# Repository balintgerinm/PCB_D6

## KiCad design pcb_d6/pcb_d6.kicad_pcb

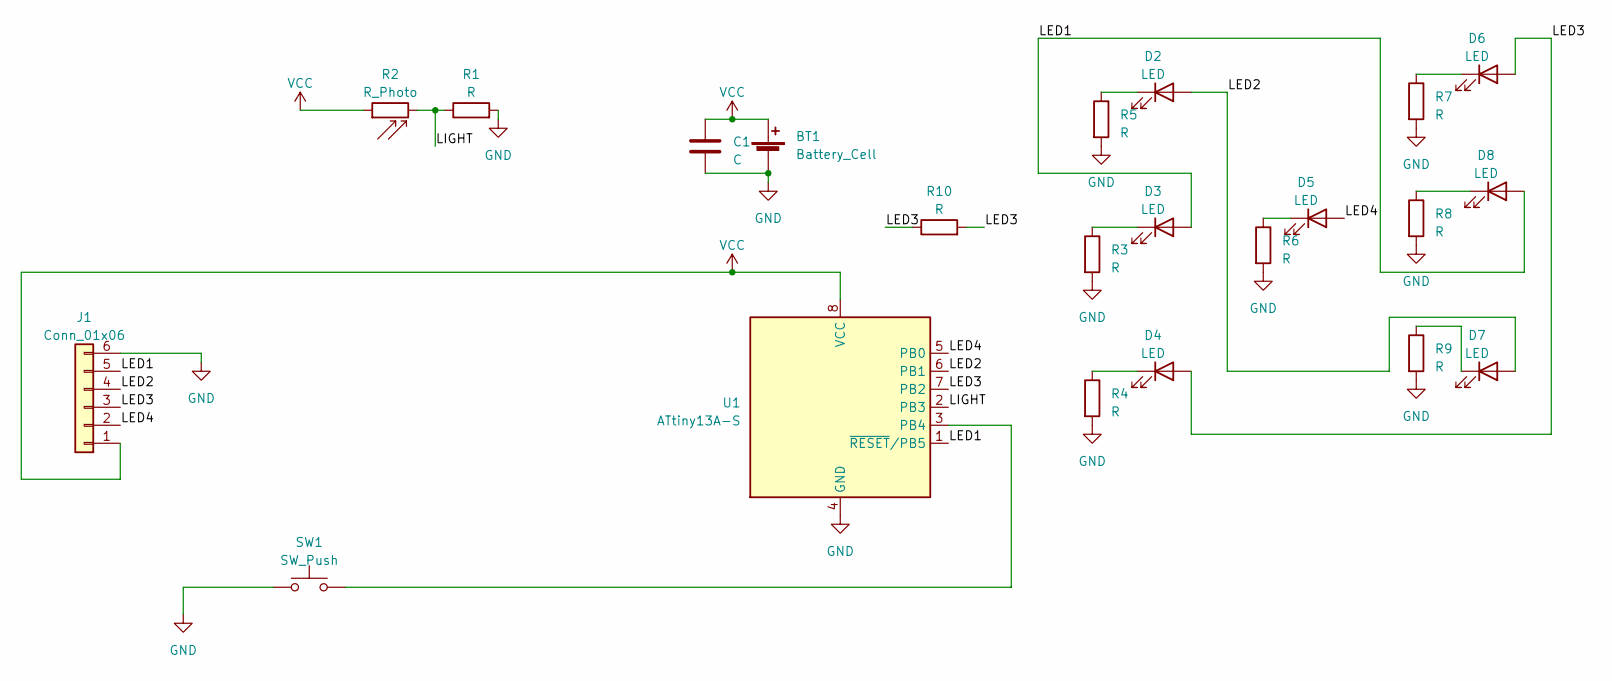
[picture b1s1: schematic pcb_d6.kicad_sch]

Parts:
BT1: Battery_Cell; BatteryHolder_Keystone_103_1x20mm
C1: C; C_0805_2012Metric_Pad1.18x1.45mm_HandSolder
D2, D3, D4, D5, D6, D7, D8: LED; LED_4
J1: Conn_01x06; PinHeader_1x06_P2.54mm_Vertical
R1, R3, R4, R5, R6, R7, R8, R9: R; R_0805_2012Metric_Pad1.20x1.40mm_HandSolder
R2: R_Photo; R_PHOTO_2
R10: R; R_1206_3216Metric
SW1: SW_Push; BUTTON_4
U1: ATtiny13A-S; SOIC-8W_5.3x5.3mm_P1.27mm

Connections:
/LED1: D3.2 (A), D8.2 (A), J1.5, U1.1 (~RESET/PB5)
/LED2: D2.2 (A), D7.2 (A), J1.4, U1.6 (PB1)
/LED3: D4.2 (A), D6.2 (A), J1.3, R10.1, R10.2, U1.7 (PB2)
/LED4: D5.2 (A), J1.2, U1.5 (PB0)
/LIGHT: R1.1, R2.2, U1.2 (PB3)
GND: BT1.2 (-), C1.2, J1.6, R1.2, R3.2, R4.2, R5.2, R6.2, R7.2, R8.2, R9.2, SW1.1, U1.4 (GND)
unnamed: D2.1 (K), R5.1
unnamed: D3.1 (K), R3.1
unnamed: D4.1 (K), R4.1
unnamed: D5.1 (K), R6.1
unnamed: D6.1 (K), R7.1
unnamed: D7.1 (K), R9.1
unnamed: D8.1 (K), R8.1
unnamed: SW1.2, U1.3 (PB4)
VCC: BT1.1 (+), C1.1, J1.1, R2.1, U1.8 (VCC)

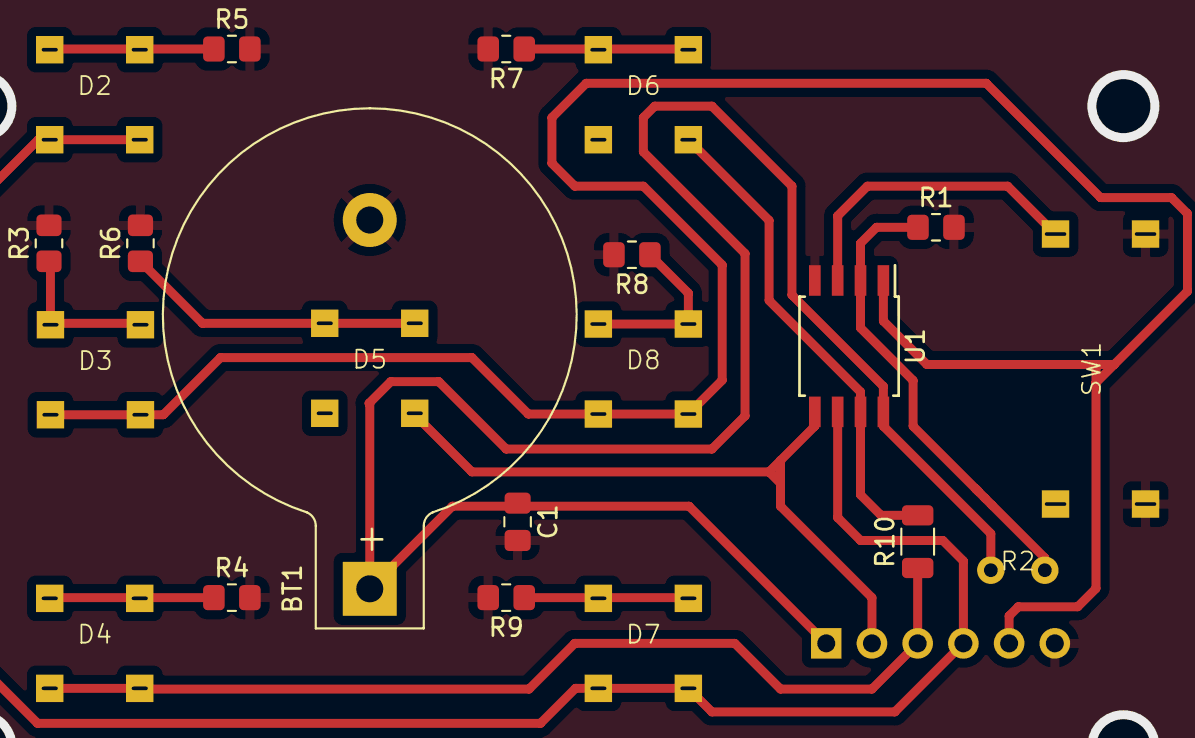
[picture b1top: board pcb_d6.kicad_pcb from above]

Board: 2 copper layers, 22 parts (1 on the bottom side), 15 nets.

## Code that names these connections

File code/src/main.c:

#include <avr/io.h>
#include <avr/interrupt.h>
#include <avr/pgmspace.h>
#include <stdlib.h>
#include <util/delay.h>


uint8_t read_pin(uint8_t pin) {
  uint8_t res = !((PINB & (1 << pin)) >> pin);
  _delay_ms(100);
  return res;
}

void doAnimation() {

for (uint8_t i = 0; i < 6; i++) {
 PORTB &= ~(0x0f); 
   switch (rand() % 6) {
          case 0:
            PORTB |= 1 << PORT1; 
            PORTB |= 1 << PORT2; 
            PORTB |= 1 << PORT3; 
            break;
          case 1:
            PORTB |= 1 << PORT0;
            break;
          case 2:
            PORTB |= 1 << PORT1;
            break;
          case 3:
            PORTB |= 1 << PORT2;
            PORTB |= 1 << PORT0;
            break;
          case 4:
            PORTB |= 1 << PORT1;
            PORTB |= 1 << PORT2;
            break;
          case 5:
            PORTB |= 1 << PORT1;
            PORTB |= 1 << PORT2;
            PORTB |= 1 << PORT0;
            break;
          default:
            break;  
          };
          _delay_ms(40);
  }
  PORTB &= ~(0x0f); 
  _delay_ms(100);
}

uint8_t state = 0;
uint32_t cnt = 0;
ISR(PCINT0_vect) {
  
   if (read_pin(PINB4)) {
      doAnimation();  

   }
  else {
          PORTB &= ~(0x0f); 
          switch (rand() % 6)
          {
          case 0:
            PORTB |= 1 << PORT1; 
            PORTB |= 1 << PORT2; 
            PORTB |= 1 << PORT3; 
            break;
          case 1:
            PORTB |= 1 << PORT0;
            break;
          case 2:
            PORTB |= 1 << PORT1;
            break;
          case 3:
            PORTB |= 1 << PORT2;
            PORTB |= 1 << PORT0;
            break;
          case 4:
            PORTB |= 1 << PORT1;
            PORTB |= 1 << PORT2;
            break;
          case 5:
            PORTB |= 1 << PORT1;
            PORTB |= 1 << PORT2;
            PORTB |= 1 << PORT0;
            break;
          default:
            break;  
          }
  }
  
}



int main() {

  
  DDRB |= 1 << DDB3; // PB3 led
  DDRB |= 1 << DDB2; // PB2 led
  DDRB |= 1 << DDB1; // PB1 led
  DDRB |= 1 << DDB0; // PB0 led
  DDRB &= ~(1 << DDB4); // PB4 gomb
  DDRB &= ~(1 << DDB5); // PB5 photoellenallas
  PORTB |= 1 << PORTB4; // felhuzoellenallas
  PORTB |= 0x00;

  GIMSK |= 1 << PCIE; // globalis interrrput engedely a labakra.
  PCMSK |= 1 << PCINT4; // Gomb interrupt enable
  srand(0);
  sei(); 

  while (1) {
    cnt++;
    //PINB |= 0x0F;
    _delay_ms(100);
  }

  return 0;
}

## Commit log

2023-03-31 Schematic
2023-04-03 PCB done
2023-04-17 code v_1.0
2023-04-19 PCB redesigned
